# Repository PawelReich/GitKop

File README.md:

# GitKop - engineering thesis

This is a repository containing my engineering thesis document, hardware and software project with simulations.

The heart of the device is a STM32H523CE microcontroller, with custom-made PCB.

**You can read the thesis** [here](https://PawelReich.github.io/GitKop). It is written in Polish. 

## Abstract

The subject of this thesis is the design and implementation of a metal detector prototype operating
in Pulse Induction technology. The theoretical part contains a historical outline of the development
of detection methods, starting from discoveries in the 19th century and ending with modern
solutions. An analysis of physical phenomena, such as Faraday’s law of induction or eddy currents,
which constitute the foundation of the device’s operation, was performed. A review of existing
popular metal detector architectures and coil types was also conducted, justifying the choice of
technology. In the practical part, the process of building a prototype based on the STM32H523CE
microcontroller with an ARM Cortex M-33 core is described in detail. The operation of the created
software implementing real-time data acquisition and signal anomaly detection through the analysis
of response time and decay slope is explained. The project assumes the creation of a functional
mobile device, along with a manufactured printed circuit board and a probe enclosed in a designed
housing made using 3D printing technology

The software is currently written in baremetal C with HAL. Accompanying software is written in Python with tkinter.

# Wykrywacz metalu - Paweł Reich 2025

## Zadania do wykonania:	
* Analiza zasad działania wykrywaczy metalu (indukcja elektromagnetyczna, impulsowe systemy detekcji).
* Opracowanie układu elektronicznego odpowiedzialnego za generowanie pola magnetycznego i odbiór sygnałów zwrotnych.
* Implementacja algorytmu analizy sygnałów detekcyjnych (np. filtrowanie szumów, identyfikacja rodzaju metalu).
* Projekt i wykonanie prototypu urządzenia, w tym obudowy oraz sondy detekcyjnej.
* Testy działania wykrywacza w różnych środowiskach oraz analiza jego skuteczności.

## Literatura:	
* "Metal Detector Studies: Research Materials", James Baker-Jarvis
* "Electromagnetics Explained: A Handbook for Wireless/RF, EMC, and High-Speed Electronics", Ron Schmitt
* Dokumentacja techniczna czujników elektromagnetycznych i mikroprocesorów użytych w projekcie (np. Arduino, ESP32).

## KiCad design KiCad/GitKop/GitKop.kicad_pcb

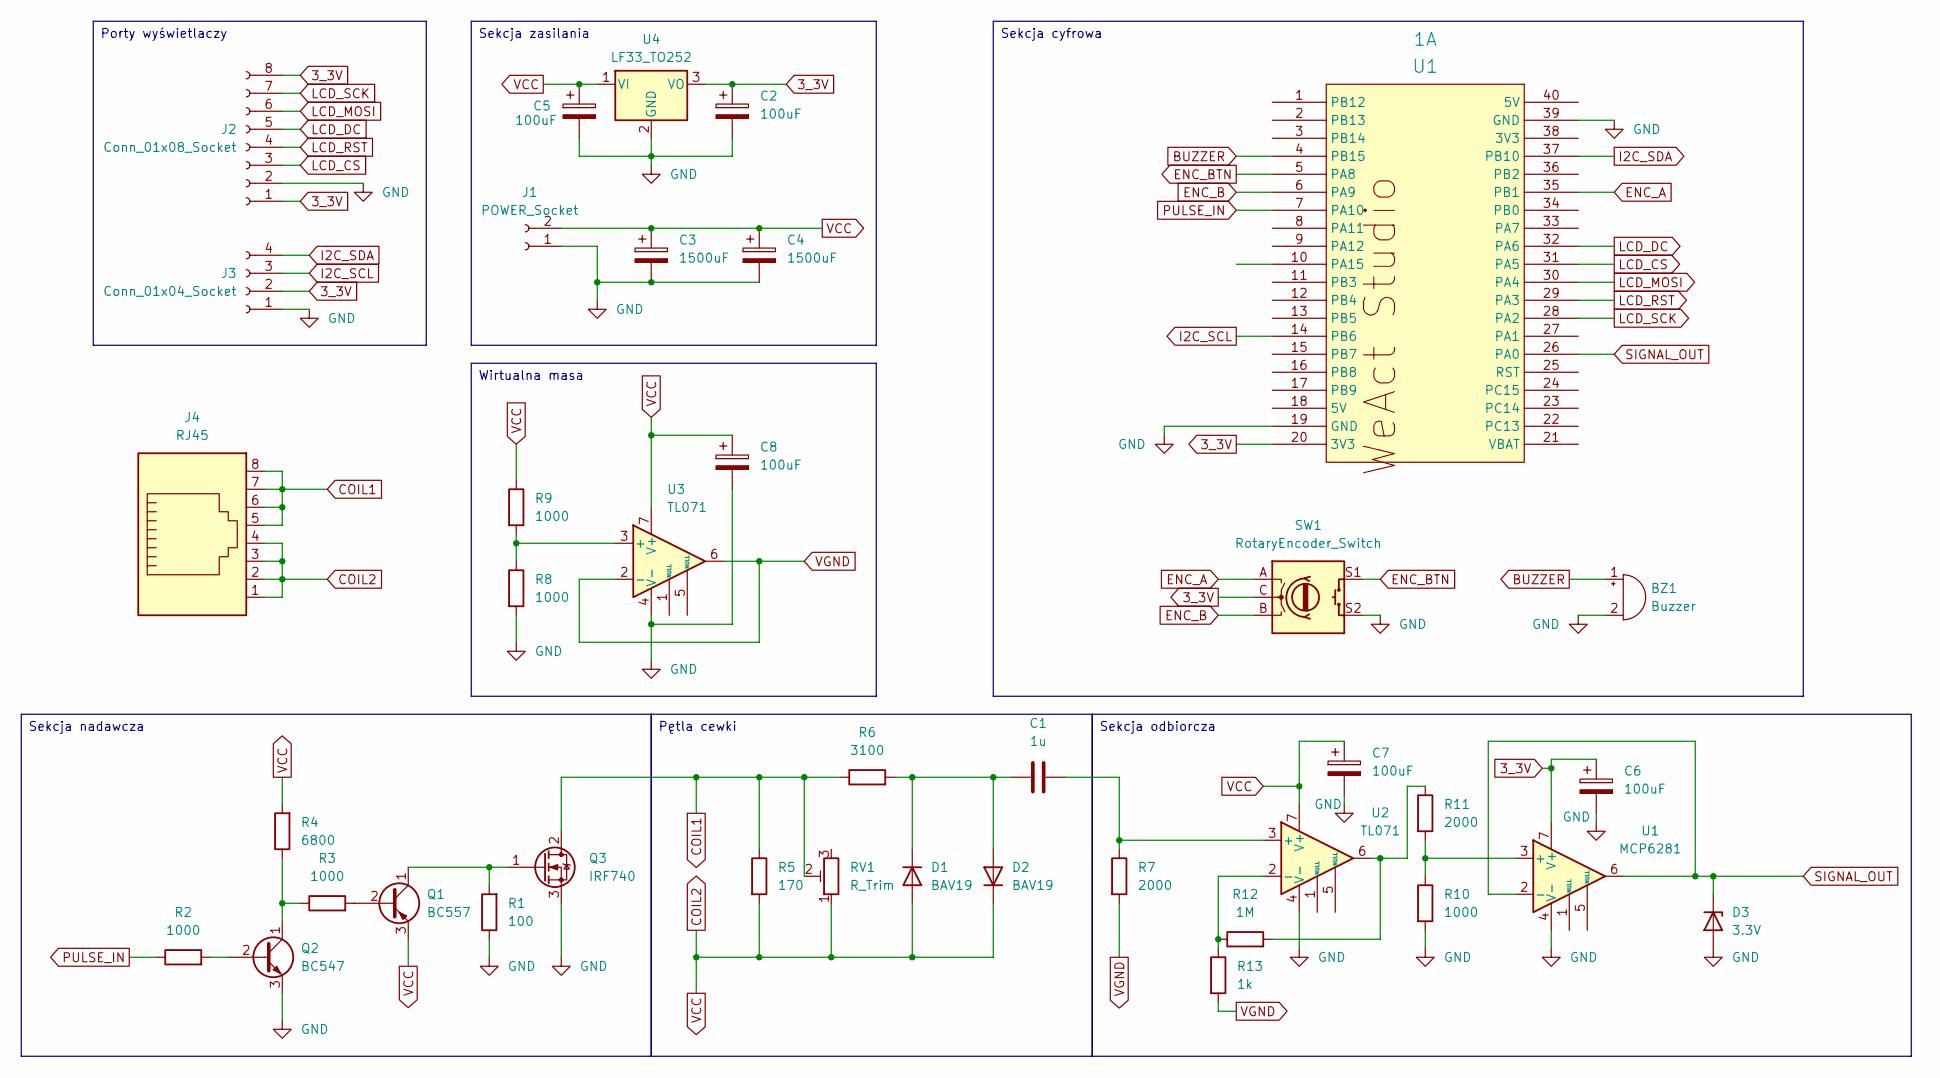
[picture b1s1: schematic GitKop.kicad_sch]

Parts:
1: U1; STM32F4x1CxU6 WeActStudio
BZ1: Buzzer; Buzzer_12x9.5RM7.6
C1: 1u; C_1206_3216Metric_Pad1.33x1.80mm_HandSolder
C2, C5, C6, C7, C8: 100uF; CP_Radial_D6.3mm_P2.50mm
C3, C4: 1500uF; CP_Radial_D10.0mm_P5.00mm
D1, D2: BAV19; D_DO-35_SOD27_P7.62mm_Horizontal
D3: 3.3V; D_MiniMELF_Handsoldering
J1: POWER_Socket; BarrelJack_Horizontal
J2: Conn_01x08_Socket; PinSocket_1x08_P2.54mm_Vertical
J3: Conn_01x04_Socket; PinSocket_1x04_P2.54mm_Vertical
J4: RJ45; MTJ881X1
Q1: BC557; TO-92_Inline
Q2: BC547; TO-92_Inline
Q3: IRF740; TO-220-3_Vertical
R1: 100; R_1206_3216Metric_Pad1.30x1.75mm_HandSolder
R2, R3, R8, R9, R10: 1000; R_1206_3216Metric_Pad1.30x1.75mm_HandSolder
R4: 6800; R_1206_3216Metric_Pad1.30x1.75mm_HandSolder
R5: 170; R_1206_3216Metric_Pad1.30x1.75mm_HandSolder
R6: 3100; R_1206_3216Metric_Pad1.30x1.75mm_HandSolder
R7, R11: 2000; R_1206_3216Metric_Pad1.30x1.75mm_HandSolder
R12: 1M; R_1206_3216Metric_Pad1.30x1.75mm_HandSolder
R13: 1k; R_1206_3216Metric_Pad1.30x1.75mm_HandSolder
RV1: R_Trim; Potentiometer_Bourns_3296W_Vertical
SW1: RotaryEncoder_Switch; RotaryEncoder_Bourns_Vertical_PEC12R-3x17F-Sxxxx
U1: MCP6281; DIP-8_W7.62mm_Socket_LongPads
U2: TL071; DIP-8_W7.62mm_Socket_LongPads
U3: TL071; SOIC-8_5.3x5.3mm_P1.27mm
U4: LF33_TO252; TO-252-2

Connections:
3_3V: 1.20 (3V3), C2.1, C6.1, J2.1, J2.8, J3.2, SW1.C, U1.7 (V+), U4.3 (VO)
BUZZER: 1.4 (PB15), BZ1.1 (+)
COIL1: J4.5, J4.6, J4.7, J4.8, Q3.2 (D), R5.1, R6.1, RV1.2
COIL2: C3.1, C4.1, C5.1, C7.1, C8.1, D1.2 (A), D2.1 (K), J1.2, J4.1, J4.2, J4.3, J4.4, Q1.3 (E), R4.2, R5.2, R9.1, RV1.1, U2.7 (V+), U3.7 (V+), U4.1 (VI)
ENC_A: 1.35 (PB1), SW1.A
ENC_B: 1.6 (PA9), SW1.B
ENC_BTN: 1.5 (PA8), SW1.S1
GND: 1.19 (GND), 1.39 (GND), BZ1.2 (-), C2.2, C3.2, C4.2, C5.2, C6.2, C7.2, C8.2, D3.2 (A), J1.1, J2.2, J3.1, Q2.3 (E), Q3.3 (S), R1.1, R8.2, R10.2, SW1.S2, U1.4 (V-), U2.4 (V-), U3.4 (V-), U4.2 (GND)
I2C_SCL: 1.14 (PB6), J3.3
I2C_SDA: 1.37 (PB10), J3.4
LCD_CS: 1.31 (PA5), J2.3
LCD_DC: 1.32 (PA6), J2.5
LCD_MOSI: 1.30 (PA4), J2.6
LCD_RST: 1.29 (PA3), J2.4
LCD_SCK: 1.28 (PA2), J2.7
unnamed: C1.1, D1.1 (K), D2.2 (A), R6.2
unnamed: Q1.2 (B), R3.2
unnamed: Q1.1 (C), Q3.1 (G), R1.2
unnamed: Q2.2 (B), R2.2
unnamed: Q2.1 (C), R3.1, R4.1
unnamed: R11.1, R12.2, U2.6
unnamed: R10.1, R11.2, U1.3 (+)
unnamed: C1.2, R7.1, U2.3 (+)
unnamed: R12.1, R13.1, U2.2 (-)
unnamed: R8.1, R9.2, U3.3 (+)
PULSE_IN: 1.7 (PA10), R2.1
SIGNAL_OUT: 1.26 (PA0), D3.1 (K), U1.2 (-), U1.6
VGND: R7.2, R13.2, U3.2 (-), U3.6

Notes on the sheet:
Sekcja nadawcza
Porty wyświetlaczy
Sekcja odbiorcza
Sekcja cyfrowa
Pętla cewki
Sekcja zasilania
Wirtualna masa

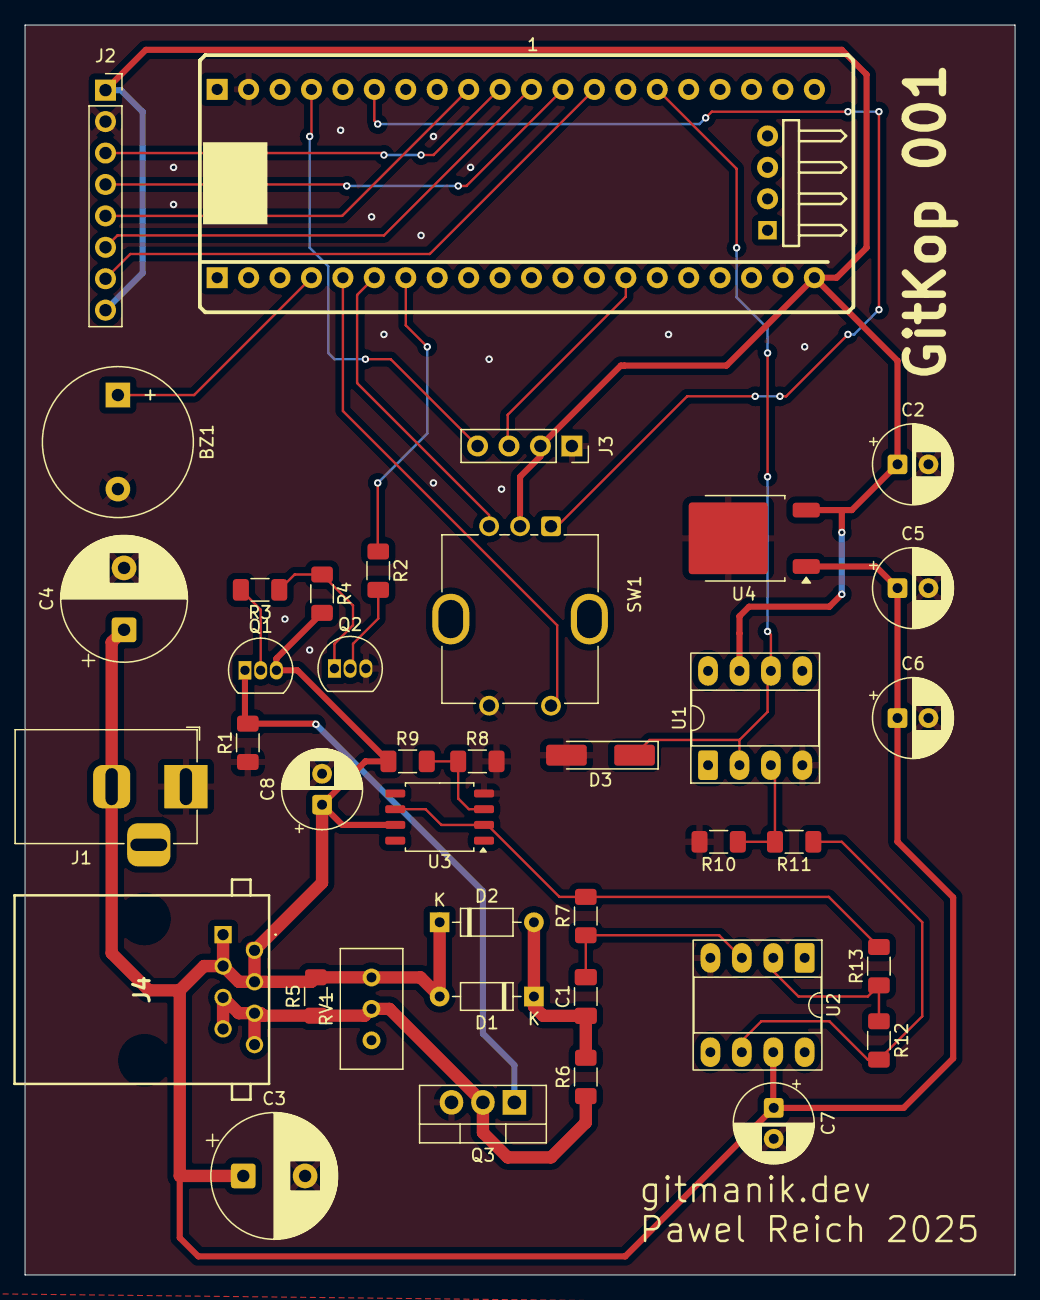
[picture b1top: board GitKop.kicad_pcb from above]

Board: 2 copper layers, 80.0 x 101.0 mm, 39 parts (0 on the bottom side), 28 nets.

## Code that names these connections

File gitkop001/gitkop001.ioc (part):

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Mcu.Name=STM32H523CCTx
Mcu.Package=LQFP48
Mcu.UserName=STM32H523CCTx
PA0.GPIOParameters=GPIO_Label
PA0.GPIO_Label=PULSE_IN
PA0.Signal=ADCx_INP0
PA10.GPIOParameters=GPIO_Speed,GPIO_Label
PA10.GPIO_Label=PULSE_OUT
PA10.GPIO_Speed=GPIO_SPEED_FREQ_VERY_HIGH
PA10.Signal=S_TIM1_CH3
PA8.GPIOParameters=GPIO_Label
PA8.GPIO_Label=ENC_BTN
PA8.Signal=GPIO_Input
PA9.GPIOParameters=GPIO_PuPd,GPIO_Label,GPIO_ModeDefaultEXTI
PA9.GPIO_Label=ENC_B
PA9.GPIO_ModeDefaultEXTI=GPIO_MODE_IT_RISING_FALLING
PA9.GPIO_PuPd=GPIO_PULLUP
PA9.Signal=GPXTI9
PB1.GPIOParameters=GPIO_PuPd,GPIO_Label,GPIO_ModeDefaultEXTI
PB1.GPIO_Label=ENC_A
PB1.GPIO_ModeDefaultEXTI=GPIO_MODE_IT_RISING_FALLING
PB1.GPIO_PuPd=GPIO_PULLUP
PB1.Signal=GPXTI1
PB10.GPIOParameters=GPIO_Speed,GPIO_PuPd,GPIO_Label,GPIO_ModeDefaultOutputPP
PB10.GPIO_Label=I2C_SDA
PB10.GPIO_ModeDefaultOutputPP=GPIO_MODE_OUTPUT_OD
PB10.GPIO_PuPd=GPIO_NOPULL
PB10.GPIO_Speed=GPIO_SPEED_FREQ_VERY_HIGH
PB10.Signal=GPIO_Output
PB14.Mode=Asynchronous
PB14.Signal=USART1_TX
PB15.GPIOParameters=GPIO_Label
PB15.GPIO_Label=BUZZER
PB15.Signal=S_TIM12_CH2
PB6.GPIOParameters=GPIO_Speed,GPIO_PuPd,GPIO_Label,GPIO_ModeDefaultOutputPP
PB6.GPIO_Label=I2C_SCL
PB6.GPIO_ModeDefaultOutputPP=GPIO_MODE_OUTPUT_OD
PB6.GPIO_PuPd=GPIO_NOPULL
PB6.GPIO_Speed=GPIO_SPEED_FREQ_VERY_HIGH
PB6.Signal=GPIO_Output
PB7.Mode=Asynchronous
PB7.Signal=USART1_RX
PC13.GPIOParameters=GPIO_Label
PC13.GPIO_Label=USER_LED
PC13.Signal=GPIO_Output
PC14-OSC32_IN(OSC32_IN).Mode=LSE-External-Oscillator
PC14-OSC32_IN(OSC32_IN).Signal=RCC_OSC32_IN
PC15-OSC32_OUT(OSC32_OUT).Mode=LSE-External-Oscillator
PC15-OSC32_OUT(OSC32_OUT).Signal=RCC_OSC32_OUT
PH0-OSC_IN(PH0).Mode=HSE-External-Oscillator
PH0-OSC_IN(PH0).Signal=RCC_OSC_IN
PH1-OSC_OUT(PH1).Mode=HSE-External-Oscillator
PH1-OSC_OUT(PH1).Signal=RCC_OSC_OUT
RCC.HSE_VALUE=8000000
RCC.SYSCLKFreq_VALUE=250000000
RCC.SYSCLKSource=RCC_SYSCLKSOURCE_PLLCLK
board=custom

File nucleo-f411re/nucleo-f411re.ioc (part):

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Mcu.Name=STM32F411R(C-E)Tx
Mcu.Package=LQFP64
Mcu.UserName=STM32F411RETx
PA0-WKUP.GPIOParameters=GPIO_Label
PA0-WKUP.GPIO_Label=PULSE_IN
PA0-WKUP.Signal=ADCx_IN0
PA10.GPIOParameters=GPIO_Label
PA10.GPIO_Label=PULSE_OUT
PA10.Signal=GPIO_Output
PA13.GPIOParameters=GPIO_Label
PA13.GPIO_Label=TMS
PA13.Mode=Serial_Wire
PA13.Signal=SYS_JTMS-SWDIO
PA14.GPIOParameters=GPIO_Label
PA14.GPIO_Label=TCK
PA14.Mode=Serial_Wire
PA14.Signal=SYS_JTCK-SWCLK
PA15.GPIOParameters=GPIO_Label
PA15.GPIO_Label=BUZZER
PA15.Signal=S_TIM2_CH1_ETR
PA2.GPIOParameters=GPIO_Label
PA2.GPIO_Label=USART_TX
PA2.Mode=Asynchronous
PA2.Signal=USART2_TX
PA3.GPIOParameters=GPIO_Label
PA3.GPIO_Label=USART_RX
PA3.Mode=Asynchronous
PA3.Signal=USART2_RX
PA5.GPIOParameters=GPIO_Label
PA5.GPIO_Label=LD2 [Green Led]
PA5.Signal=GPIO_Output
PB0.Mode=TX_Only_Simplex_Unidirect_Master
PB0.Signal=SPI5_SCK
PB3.GPIOParameters=GPIO_Label
PB3.GPIO_Label=SWO
PB3.Signal=SYS_JTDO-SWO
PB8.Mode=TX_Only_Simplex_Unidirect_Master
PB8.Signal=SPI5_MOSI
PC0.GPIOParameters=GPIO_Label
PC0.GPIO_Label=LCD_DC
PC0.Signal=GPIO_Output
PC1.GPIOParameters=GPIO_Label
PC1.GPIO_Label=LCD_RESET
PC1.Signal=GPIO_Output
PC13-ANTI_TAMP.GPIOParameters=GPIO_Label,GPIO_ModeDefaultEXTI
PC13-ANTI_TAMP.GPIO_Label=B1 [Blue PushButton]
PC13-ANTI_TAMP.GPIO_ModeDefaultEXTI=GPIO_MODE_IT_FALLING
PC13-ANTI_TAMP.Signal=GPXTI13
PC14-OSC32_IN.Signal=RCC_OSC32_IN
PC15-OSC32_OUT.Signal=RCC_OSC32_OUT
PC3.GPIOParameters=GPIO_Label
PC3.GPIO_Label=LCD_CS
PC3.Signal=GPIO_Output
PH0\ -\ OSC_IN.Mode=HSE-External-Clock-Source
PH0\ -\ OSC_IN.Signal=RCC_OSC_IN
PH1\ -\ OSC_OUT.Mode=HSE-External-Clock-Source
PH1\ -\ OSC_OUT.Signal=RCC_OSC_OUT
RCC.HSE_VALUE=8000000
RCC.SYSCLKFreq_VALUE=72000000
RCC.SYSCLKSource=RCC_SYSCLKSOURCE_PLLCLK
board=NUCLEO-F411RE
boardIOC=true

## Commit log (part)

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2024-04-09 Falstad circuits
2024-04-11 Create .gitignore for LTSpice files
2024-04-11 Removed old .tran command
2024-04-15 7.4V, IRF7401, ESP32 150mA
2024-04-25 Zmiana IRF7401 na IRF740
2024-04-27 added schottky diode
2024-04-27 delay 500us -> 250us on clk
2024-04-28 altium first commit
2024-06-01 Simple ESP32-based pulse generator code
2024-07-14 ESP32: Timer-based pulse generator code
2024-07-14 ESP32: Changed IDE from VSCode to CLion
2024-12-06 kicad
2025-03-01 pierwszy schemat
2025-08-23 tex: First commit
2025-08-23 tex: Fix polish lang
2025-08-25 kicad: Remove useless files
2025-08-30 esp32: Clean timer-based PULSE_OUT code
2025-08-30 doc: WIP budowa (ESP32)
2025-09-02 esp32: Broken ADC impl
2025-09-03 doc: timery adc dma + stm32.png
2025-09-05 doc: todonotes package
2025-09-07 meas: 06.09 measurements
2025-09-07 nucleo-f411re: basic code
2025-09-07 kicad: update
2025-09-07 doc: upd
2025-09-08 nucleo-f411re: 1/5 of original pulse width
2025-10-05 Altium, bluepill: Removed
2025-10-05 esp32: Removed
2025-10-05 f411re: Added ILI9341 driver
2025-10-05 f411re: enabled SPI, moved to GitKop.h/.c
2025-10-07 KiCad: Update before ordering
2025-10-07 code: Fixed ILI9341 colors
2025-10-07 kicad: 0th version
2025-10-31 gitkop001
2025-11-04 kicad: 1st version
2025-11-12 doc: BibTeX
2025-11-16 doc: Removed example files
2025-11-16 doc: Moved images to img/
2025-11-17 doc: sort bibtex biblio by usage
2025-11-17 doc: intro v0
2025-11-18 doc: wstep -> wstep i cel pracy
2025-11-18 doc: rm Rozdzial2
2025-11-23 doc: added citations to build
2025-11-23 doc: Fixed wrong \includepdf args
2025-11-24 doc: pcb layout
2025-11-24 doc: github workflow
2025-11-24 doc: wstep poddaje sie
2025-11-24 doc: przeglad: elektromagnetyzm v0
2025-11-24 doc: oznazcenia
2025-11-25 doc: schemat sekcji sterujacej
2025-11-25 doc: alternator figure
2025-11-25 doc: gitignore svg-inkscape output
2025-11-25 doc: przeglad: approx
2025-11-25 doc: wstep: change todo
2025-11-25 dump
2025-11-25 doc: use latex-action for building
2025-11-26 doc: wyprowadzenie diffusion
2025-11-26 chang
2025-11-26 doc: Podzial przeglad.tex na Przeglad/*
2025-11-26 README
2025-11-26 doc: 3D Render PCB
2025-11-26 doc: Renamed most of bib entries to match their ID
2025-11-27 doc: Sondy
2025-11-27 doc: jeden appendix na dokument
2025-11-27 doc: draft problemow rodzajow wykrywaczy
2025-11-27 doc: stub celu pracy
2025-11-28 doc: po recenzji 27.11
2025-11-30 doc: Dyfuzja: skladowe rownan
2025-12-02 doc: Przeglad: cytowanie
2025-12-02 doc: Porownawcza: BFO
2025-12-02 doc: Dyfuzja: Skin effect
2025-12-02 KiCad: export step model
2025-12-06 doc: final draft teorii
2025-12-08 doc: po recencji 05.12
2025-12-08 sch: Sprzatanie
2025-12-09 submodules: Add STMH523CoreBoard
2025-12-09 submodules: Drop ILI9341 and STMF411CoreBoard
2025-12-10 soft: plotter worky but no dual adc and wrong algho
2025-12-10 kicad: updated
2025-12-10 3d: renders
2025-12-10 doc: przetlumaczone obrazki
2025-12-10 doc: tikzset
2025-12-10 doc: sprzatanie stale plikow
2025-12-14 plotter: modular and worky
2025-12-14 doc: budowa: powoli do celu
2025-12-17 edf converter
2025-12-17 doc: irf740 bib vishay
2025-12-19 plotter: fix fft
2025-12-19 doc: drop todo pi blok
2025-12-19 prez
2025-12-19 doc: wyliczona wartosc sondy
2026-01-03 code: TIM1-based PWM with analog watchdog
2026-01-03 measurement
2026-01-04 doc: SS PCB
2026-01-04 doc: wykres odpowiedzi cewki
2026-01-04 blisko
2026-01-06 06.01
2026-01-07 doc: oznaczenia i symbole
2026-01-07 doc: abstract
2026-01-07 doc: equation - tozsamosc wektorowa
2026-01-07 doc: frac -> przecinek
2026-01-07 doc: 3000 -> 2500
2026-01-07 sch: r5, r6 real values
2026-01-07 doc: img/testy
2026-01-07 doc: drop tranzystory.png
2026-01-07 doc: ss schematow
2026-01-07 doc: wykrywacz wysyla pakiet 10hz
2026-01-07 doc: pcb.pdf
2026-01-07 sch: cleanup and textbox
2026-01-07 doc: ss stm32
2026-01-07 sch: export to png
2026-01-07 doc: . -> ,
2026-01-07 doc: ref cewka_odp
2026-01-07 doc: irf740 bib
2026-01-07 doc: zrodlo st micro
2026-01-07 sch: zmiescic bfo
2026-01-07 sch: fix justowania
2026-01-07 doc: inside the mteal detector 2015
2026-01-07 doc: rozszerzony opis obudowy
2026-01-07 doc: rozszerzony opis pcb
2026-01-07 doc: zmiana wymiarow rysunkow
2026-01-07 doc: update ss programu
2026-01-07 doc: lepszy pulse_out
2026-01-07 doc: tlumaczenie oecd
2026-01-07 doc: test dzialania update
2026-01-07 doc: update schem
2026-01-07 doc: sprzatanie testy
2026-01-07 doc: drop starych img/budowa
2026-01-07 edfplot: pliki generujace wykresy
2026-01-07 edfplotter: separate repo
2026-01-07 doc: fix literowek
2026-01-07 zephyr: drop
2026-01-07 doc: podsumowanie
2026-01-07 doc: podsumowanie update
2026-01-08 doc: oswiadczenie, projekt dyplomowy inzynierski
2026-01-08 sch: fix mcp6281 vcc
2026-01-08 meas: drop old measurements
2026-01-08 gitkop001: SSD1306 code and ENC GPIO
2026-01-08 meas: new pulse_out
2026-01-08 plotter: final ver
2026-01-18 nucleo-f411re: drop
2026-01-18 actions: Build prez.tex
2026-01-18 fixup! prez
2026-01-20 chore: tidying
2026-01-20 chore: Beautify README
2026-01-20 chore: Remove stale KiCad files
2026-01-21 chore: Upload thesis to GH Pages
2026-01-21 chore: Fix presentation GH Action
2026-01-21 chore: Update README with abstract and link to PDF
